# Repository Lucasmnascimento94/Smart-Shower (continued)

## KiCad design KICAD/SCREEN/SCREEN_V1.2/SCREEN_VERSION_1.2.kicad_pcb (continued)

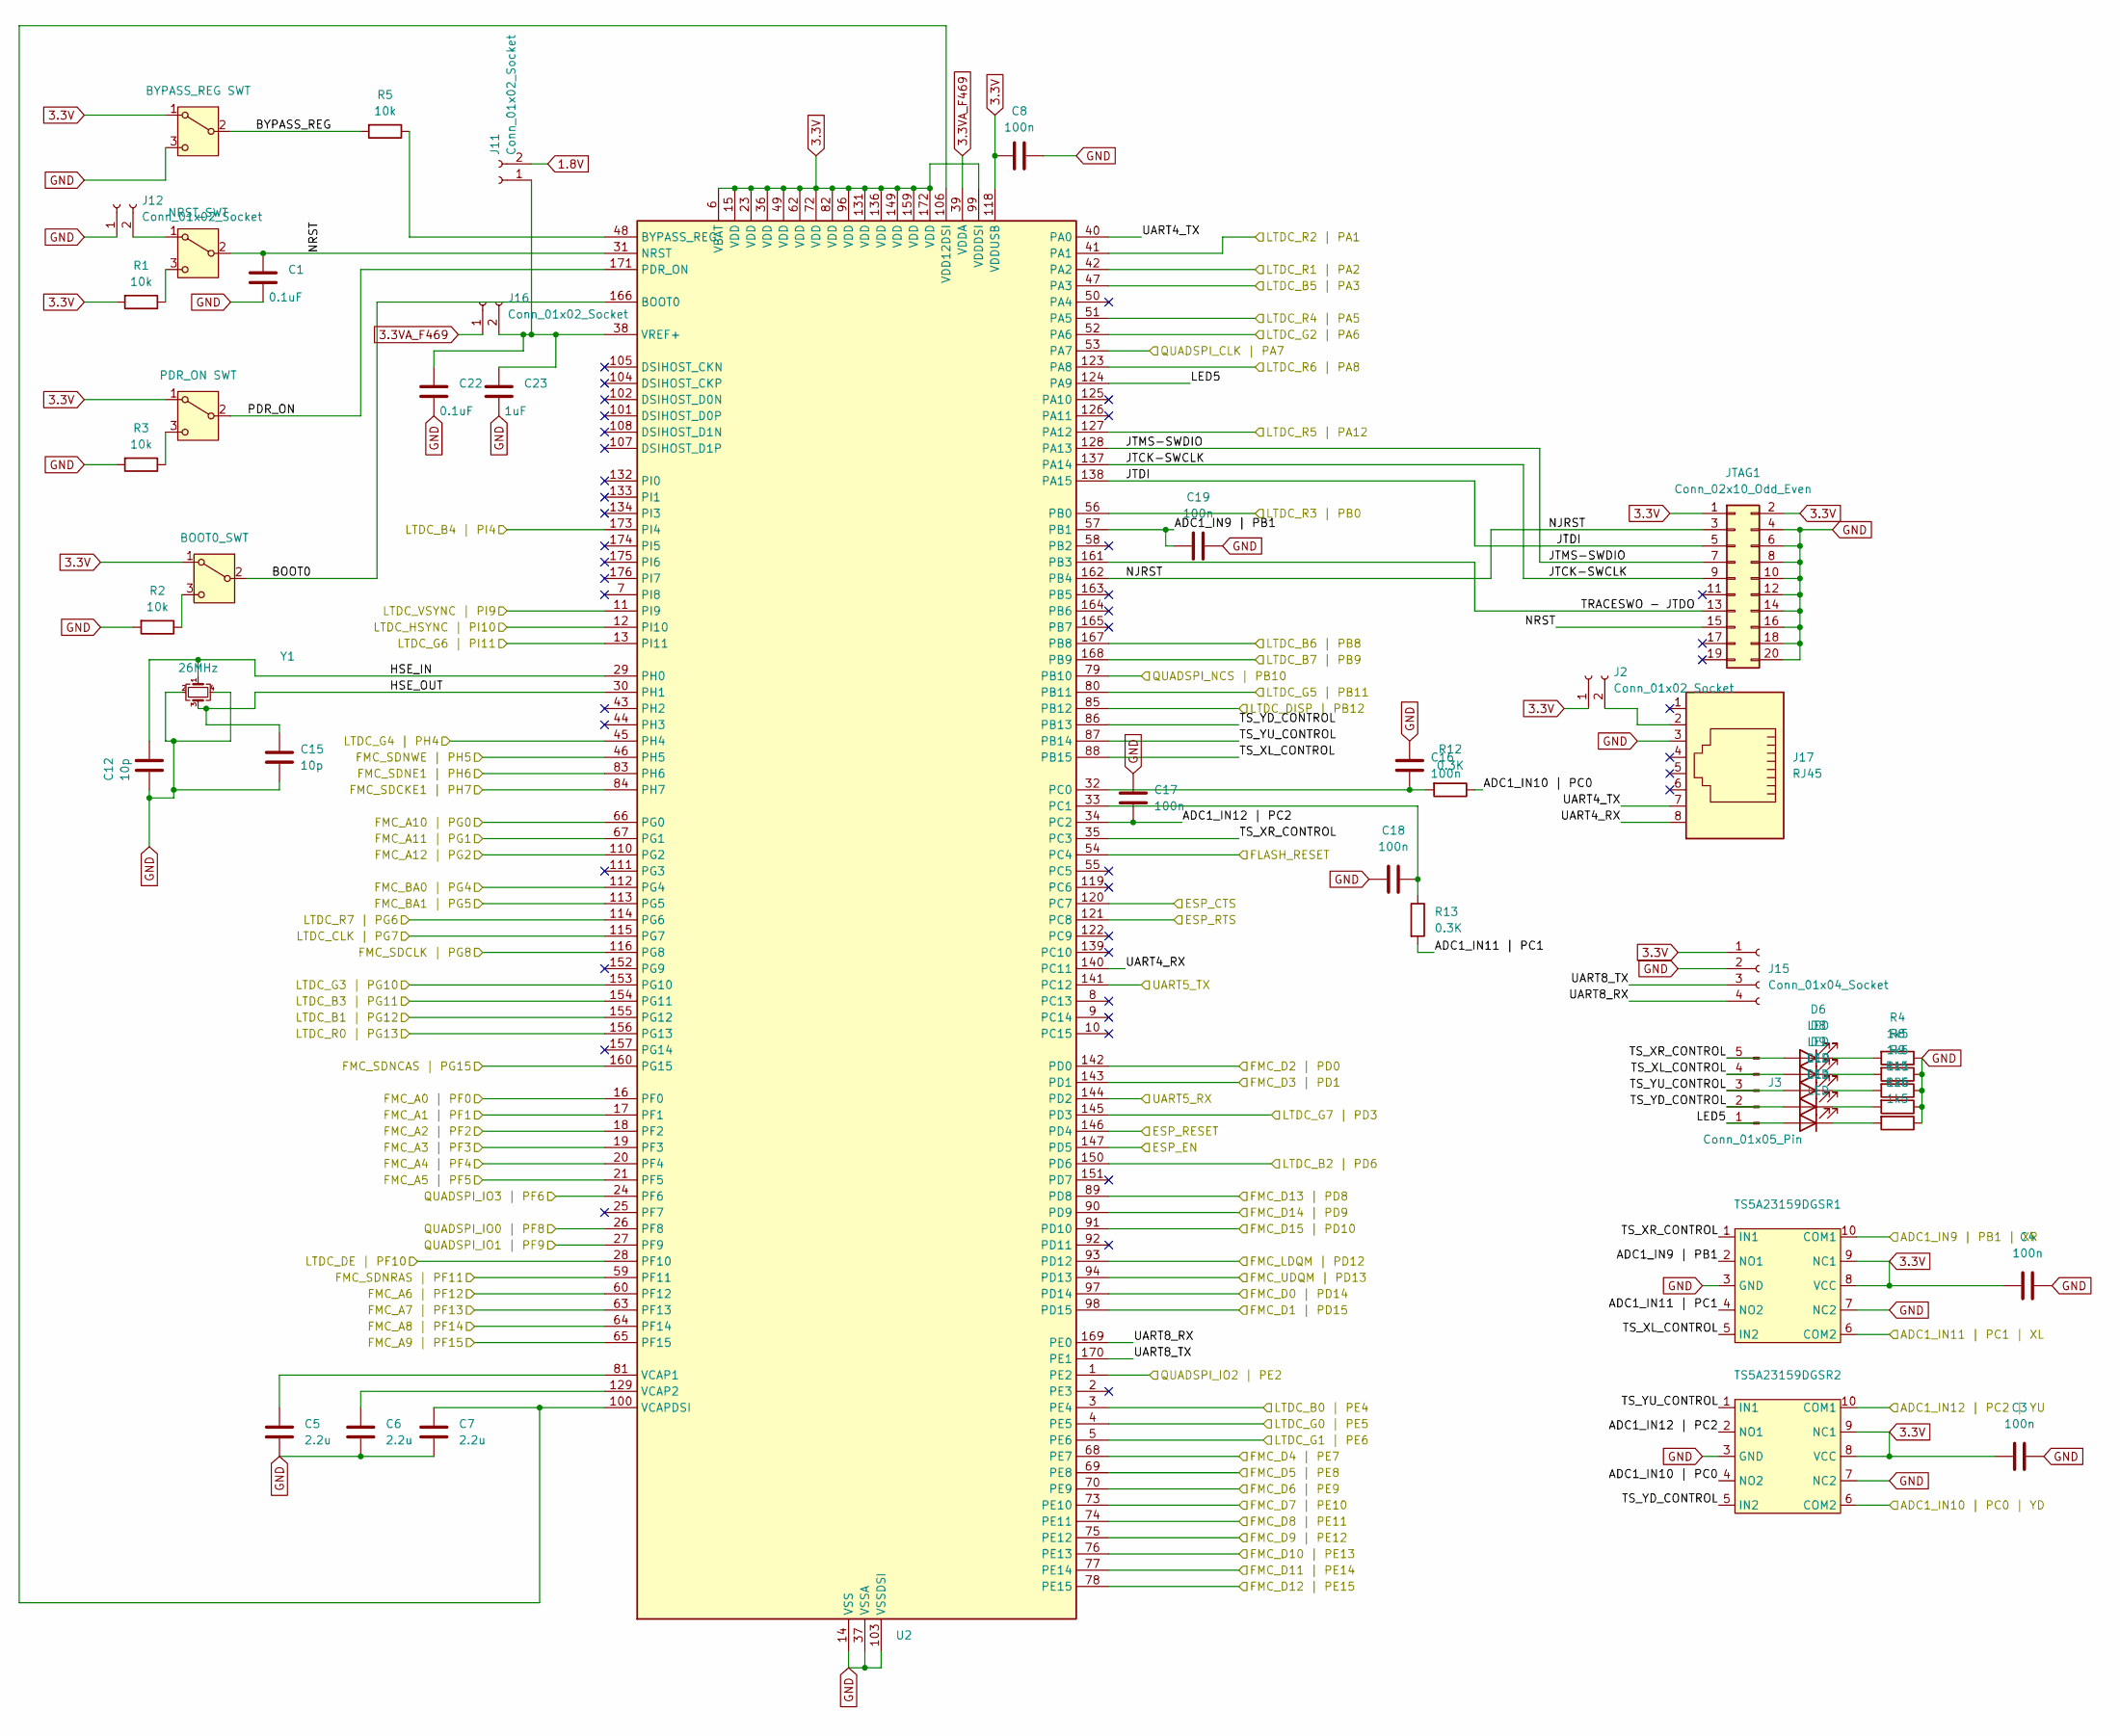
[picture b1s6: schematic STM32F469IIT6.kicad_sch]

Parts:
C1, C22: 0.1uF; C_0402_1005Metric
C3, C4, C8, C16, C17, C18, C19: 100n; C_0402_1005Metric
C5, C6, C7: 2.2u; C_0402_1005Metric
C12, C15: 10p; C_0402_1005Metric
C23: 1uF; C_0402_1005Metric
D6, D8, D9, D10, D11: LED; LED_0603_1608Metric
J2, J11, J12, J16: Conn_01x02_Socket; PinSocket_1x02_P2.54mm_Vertical
J3: Conn_01x05_Pin; PinSocket_1x05_P2.54mm_Vertical
J15: Conn_01x04_Socket; PinSocket_1x04_P2.54mm_Vertical
J17: RJ45; RJ45_Pulse_JXD6-0001NL_Horizontal
JTAG1: Conn_02x10_Odd_Even; IDC-Header_2x10_P2.54mm_Vertical
R1, R2, R3, R5: 10k; R_0402_1005Metric
R4, R8, R9, R11, R26: 1k5; R_0402_1005Metric
R12, R13: 0.3K; R_0402_1005Metric
SW1: BOOT0_SWT; SW_Slide_SPDT_Straight_CK_OS102011MS2Q
SW2: NRST_SWT; SW_Slide_SPDT_Straight_CK_OS102011MS2Q
SW3: PDR_ON SWT; SW_Slide_SPDT_Straight_CK_OS102011MS2Q
SW4: BYPASS_REG SWT; SW_Slide_SPDT_Straight_CK_OS102011MS2Q
TS5A23159DGSR1, TS5A23159DGSR2: TS5A23159DGSR
U2: STM32F469IITx; LQFP-176_24x24mm_P0.5mm
Y1: 26MHz; Crystal_SMD_3225-4Pin_3.2x2.5mm_HandSoldering

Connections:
1.8V: J11.2; also elsewhere on the board
3.3V: C3.1, C4.1, C8.1, J2.1, J15.1, JTAG1.1, JTAG1.2, R1.2, SW1.1 (A), SW3.1 (A), SW4.1 (A), TS5A23159DGSR1.8 (VCC), TS5A23159DGSR1.9 (NC1), TS5A23159DGSR2.8 (VCC), TS5A23159DGSR2.9 (NC1), U2.6 (VBAT), U2.15 (VDD), U2.23 (VDD), U2.36 (VDD), U2.49 (VDD), U2.62 (VDD), U2.72 (VDD), U2.82 (VDD), U2.96 (VDD), U2.99 (VDDDSI), U2.118 (VDDUSB), U2.131 (VDD), U2.136 (VDD), U2.149 (VDD), U2.159 (VDD), U2.172 (VDD); also elsewhere on the board
3.3VA_F469: J16.1, U2.39 (VDDA); also elsewhere on the board
/ESP-12E/CTS: U2.120 (PC7); also elsewhere on the board
/ESP-12E/EN: U2.147 (PD5); also elsewhere on the board
/ESP-12E/ESP_RX: U2.141 (PC12); also elsewhere on the board
/ESP-12E/ESP_TX: U2.144 (PD2); also elsewhere on the board
/ESP-12E/RST: U2.146 (PD4); also elsewhere on the board
/ESP-12E/RTS: U2.121 (PC8); also elsewhere on the board
/Flash - W25M512JVFIQ TR/CLK: U2.53 (PA7); also elsewhere on the board
/Flash - W25M512JVFIQ TR/CS: U2.79 (PB10); also elsewhere on the board
/Flash - W25M512JVFIQ TR/IO0: U2.26 (PF8); also elsewhere on the board
/Flash - W25M512JVFIQ TR/IO1: U2.27 (PF9); also elsewhere on the board
/Flash - W25M512JVFIQ TR/IO2: U2.1 (PE2); also elsewhere on the board
/Flash - W25M512JVFIQ TR/IO3: U2.24 (PF6); also elsewhere on the board
/Flash - W25M512JVFIQ TR/RESET: U2.54 (PC4); also elsewhere on the board
/LCD/B0: U2.3 (PE4); also elsewhere on the board
/LCD/B1: U2.155 (PG12); also elsewhere on the board
/LCD/B2: U2.150 (PD6); also elsewhere on the board
/LCD/B3: U2.154 (PG11); also elsewhere on the board
/LCD/B4: U2.173 (PI4); also elsewhere on the board
/LCD/B5: U2.47 (PA3); also elsewhere on the board
/LCD/B6: U2.167 (PB8); also elsewhere on the board
/LCD/B7: U2.168 (PB9); also elsewhere on the board
/LCD/DCLK: U2.115 (PG7); also elsewhere on the board
/LCD/DEN: U2.28 (PF10); also elsewhere on the board
/LCD/DISP: U2.85 (PB12); also elsewhere on the board
/LCD/G0: U2.4 (PE5); also elsewhere on the board
/LCD/G1: U2.5 (PE6); also elsewhere on the board
/LCD/G2: U2.52 (PA6); also elsewhere on the board
/LCD/G3: U2.153 (PG10); also elsewhere on the board
/LCD/G4: U2.45 (PH4); also elsewhere on the board
/LCD/G5: U2.80 (PB11); also elsewhere on the board
/LCD/G6: U2.13 (PI11); also elsewhere on the board
/LCD/G7: U2.145 (PD3); also elsewhere on the board
/LCD/HSYNC: U2.12 (PI10); also elsewhere on the board
/LCD/R0: U2.156 (PG13); also elsewhere on the board
/LCD/R1: U2.42 (PA2); also elsewhere on the board
/LCD/R2: U2.41 (PA1); also elsewhere on the board
/LCD/R3: U2.56 (PB0); also elsewhere on the board
/LCD/R4: U2.51 (PA5); also elsewhere on the board
/LCD/R5: U2.127 (PA12); also elsewhere on the board
/LCD/R6: U2.123 (PA8); also elsewhere on the board
/LCD/R7: U2.114 (PG6); also elsewhere on the board
/LCD/VSYNC: U2.11 (PI9); also elsewhere on the board
/LCD/XL_ADC: TS5A23159DGSR1.6 (COM2); also elsewhere on the board
/LCD/XR_ADC: TS5A23159DGSR1.10 (COM1); also elsewhere on the board
/LCD/YD_ADC: TS5A23159DGSR2.6 (COM2); also elsewhere on the board
/LCD/YU_ADC: TS5A23159DGSR2.10 (COM1); also elsewhere on the board
/STM32F469IIT6/ADC1_IN9 | PB1: C19.1, TS5A23159DGSR1.2 (NO1), U2.57 (PB1)
/STM32F469IIT6/ADC1_IN10 | PC0: R12.1, TS5A23159DGSR2.4 (NO2)
/STM32F469IIT6/ADC1_IN11 | PC1: R13.2, TS5A23159DGSR1.4 (NO2)
/STM32F469IIT6/ADC1_IN12 | PC2: C17.2, TS5A23159DGSR2.2 (NO1), U2.34 (PC2)
/STM32F469IIT6/BOOT0: SW1.2 (B), U2.166 (BOOT0); also elsewhere on the board
/STM32F469IIT6/BYPASS_REG: R5.2, SW4.2 (B); also elsewhere on the board
/STM32F469IIT6/FMC_A0 | PF0: U2.16 (PF0); also elsewhere on the board
/STM32F469IIT6/FMC_A1 | PF1: U2.17 (PF1); also elsewhere on the board
/STM32F469IIT6/FMC_A2 | PF2: U2.18 (PF2); also elsewhere on the board
/STM32F469IIT6/FMC_A3 | PF3: U2.19 (PF3); also elsewhere on the board
/STM32F469IIT6/FMC_A4 | PF4: U2.20 (PF4); also elsewhere on the board
/STM32F469IIT6/FMC_A5 | PF5: U2.21 (PF5); also elsewhere on the board
/STM32F469IIT6/FMC_A6 | PF12: U2.60 (PF12); also elsewhere on the board
/STM32F469IIT6/FMC_A7 | PF13: U2.63 (PF13); also elsewhere on the board
/STM32F469IIT6/FMC_A8 | PF14: U2.64 (PF14); also elsewhere on the board
/STM32F469IIT6/FMC_A9 | PF15: U2.65 (PF15); also elsewhere on the board
/STM32F469IIT6/FMC_A10 | PG0: U2.66 (PG0); also elsewhere on the board
/STM32F469IIT6/FMC_A11 | PG1: U2.67 (PG1); also elsewhere on the board
/STM32F469IIT6/FMC_A12 | PG2: U2.110 (PG2); also elsewhere on the board
/STM32F469IIT6/FMC_BA0 | PG4: U2.112 (PG4); also elsewhere on the board
/STM32F469IIT6/FMC_BA1 | PG5: U2.113 (PG5); also elsewhere on the board
/STM32F469IIT6/FMC_D0 | PD14: U2.97 (PD14); also elsewhere on the board
/STM32F469IIT6/FMC_D1 | PD15: U2.98 (PD15); also elsewhere on the board
/STM32F469IIT6/FMC_D2 | PD0: U2.142 (PD0); also elsewhere on the board
/STM32F469IIT6/FMC_D3 | PD1: U2.143 (PD1); also elsewhere on the board
/STM32F469IIT6/FMC_D4 | PE7: U2.68 (PE7); also elsewhere on the board
/STM32F469IIT6/FMC_D5 | PE8: U2.69 (PE8); also elsewhere on the board
/STM32F469IIT6/FMC_D6 | PE9: U2.70 (PE9); also elsewhere on the board
/STM32F469IIT6/FMC_D7 | PE10: U2.73 (PE10); also elsewhere on the board
/STM32F469IIT6/FMC_D8 | PE11: U2.74 (PE11); also elsewhere on the board
/STM32F469IIT6/FMC_D9 | PE12: U2.75 (PE12); also elsewhere on the board
/STM32F469IIT6/FMC_D10 | PE13: U2.76 (PE13); also elsewhere on the board
/STM32F469IIT6/FMC_D11 | PE14: U2.77 (PE14); also elsewhere on the board
/STM32F469IIT6/FMC_D12 | PE15: U2.78 (PE15); also elsewhere on the board
/STM32F469IIT6/FMC_D13 | PD8: U2.89 (PD8); also elsewhere on the board
/STM32F469IIT6/FMC_D14 | PD9: U2.90 (PD9); also elsewhere on the board
/STM32F469IIT6/FMC_D15 | PD10: U2.91 (PD10); also elsewhere on the board
/STM32F469IIT6/FMC_LDQM | PD12: U2.93 (PD12); also elsewhere on the board
/STM32F469IIT6/FMC_SDCKE1 | PH7: U2.84 (PH7); also elsewhere on the board
/STM32F469IIT6/FMC_SDCLK | PG8: U2.116 (PG8); also elsewhere on the board
/STM32F469IIT6/FMC_SDNCAS | PG15: U2.160 (PG15); also elsewhere on the board
/STM32F469IIT6/FMC_SDNE1 | PH6: U2.83 (PH6); also elsewhere on the board
/STM32F469IIT6/FMC_SDNRAS | PF11: U2.59 (PF11); also elsewhere on the board
/STM32F469IIT6/FMC_SDNWE | PH5: U2.46 (PH5); also elsewhere on the board
/STM32F469IIT6/FMC_UDQM | PD13: U2.94 (PD13); also elsewhere on the board
/STM32F469IIT6/HSE_IN: C12.1, U2.29 (PH0), Y1.1
/STM32F469IIT6/HSE_OUT: C15.1, U2.30 (PH1), Y1.3
/STM32F469IIT6/JTCK-SWCLK: JTAG1.9, U2.137 (PA14)
/STM32F469IIT6/JTDI: JTAG1.5, U2.138 (PA15)
/STM32F469IIT6/JTMS-SWDIO: JTAG1.7, U2.128 (PA13)
/STM32F469IIT6/LED5: D11.2 (A), J3.1, U2.124 (PA9)
/STM32F469IIT6/NJRST: JTAG1.3, U2.162 (PB4)
/STM32F469IIT6/NRST: C1.2, JTAG1.15, SW2.2 (B), U2.31 (NRST); also elsewhere on the board
/STM32F469IIT6/PDR_ON: SW3.2 (B), U2.171 (PDR_ON); also elsewhere on the board
/STM32F469IIT6/TRACESWO - JTDO: JTAG1.13, U2.161 (PB3)
/STM32F469IIT6/TS_XL_CONTROL: D8.2 (A), J3.4, TS5A23159DGSR1.5 (IN2), U2.88 (PB15)
/STM32F469IIT6/TS_XR_CONTROL: D6.2 (A), J3.5, TS5A23159DGSR1.1 (IN1), U2.35 (PC3)
/STM32F469IIT6/TS_YD_CONTROL: D10.2 (A), J3.2, TS5A23159DGSR2.5 (IN2), U2.86 (PB13)
/STM32F469IIT6/TS_YU_CONTROL: D9.2 (A), J3.3, TS5A23159DGSR2.1 (IN1), U2.87 (PB14)
/STM32F469IIT6/UART4_RX: J17.8, U2.140 (PC11)
/STM32F469IIT6/UART4_TX: J17.7, U2.40 (PA0)
/STM32F469IIT6/UART8_RX: J15.4, U2.169 (PE0)
/STM32F469IIT6/UART8_TX: J15.3, U2.170 (PE1)
GND: C1.1, C3.2, C4.2, C5.2, C6.2, C7.2, C8.2, C12.2, C15.2, C16.1, C17.1, C18.1, C19.2, C22.1, C23.1, J12.1, J15.2, J17.3, JTAG1.4, JTAG1.6, JTAG1.8, JTAG1.10, JTAG1.12, JTAG1.14, JTAG1.16, JTAG1.18, JTAG1.20, R2.2, R3.2, R4.1, R8.1, R9.1, R11.1, R26.1, SW4.3 (C), TS5A23159DGSR1.3 (GND), TS5A23159DGSR1.7 (NC2), TS5A23159DGSR2.3 (GND), TS5A23159DGSR2.7 (NC2), U2.14 (VSS), U2.22 (VSS), U2.37 (VSSA), U2.61 (VSS), U2.71 (VSS), U2.95 (VSS), U2.103 (VSSDSI), U2.109 (VSSDSI), U2.117 (VSS), U2.130 (VSS), U2.135 (VSS), U2.148 (VSS), U2.158 (VSS), Y1.2, Y1.4; also elsewhere on the board
unnamed: D6.1 (K), R4.2
unnamed: D8.1 (K), R8.2
unnamed: D9.1 (K), R9.2
unnamed: D10.1 (K), R11.2
unnamed: D11.1 (K), R26.2
unnamed: J2.2, J17.2
unnamed: C22.2, C23.2, J11.1, J16.2, U2.38 (VREF+)
unnamed 137: J12.2, SW2.1 (A); also elsewhere on the board
unnamed 140: R2.1, SW1.3 (C); also elsewhere on the board
unnamed 141: R1.1, SW2.3 (C); also elsewhere on the board
unnamed 142: R3.1, SW3.3 (C); also elsewhere on the board
unnamed: R5.1, U2.48 (BYPASS_REG)
unnamed: C16.2, R12.2, U2.32 (PC0)
unnamed: C18.2, R13.1, U2.33 (PC1)
unnamed: C5.1, U2.81 (VCAP1)
unnamed: C6.1, U2.129 (VCAP2)
unnamed: C7.1, U2.100 (VCAPDSI), U2.106 (VDD12DSI)

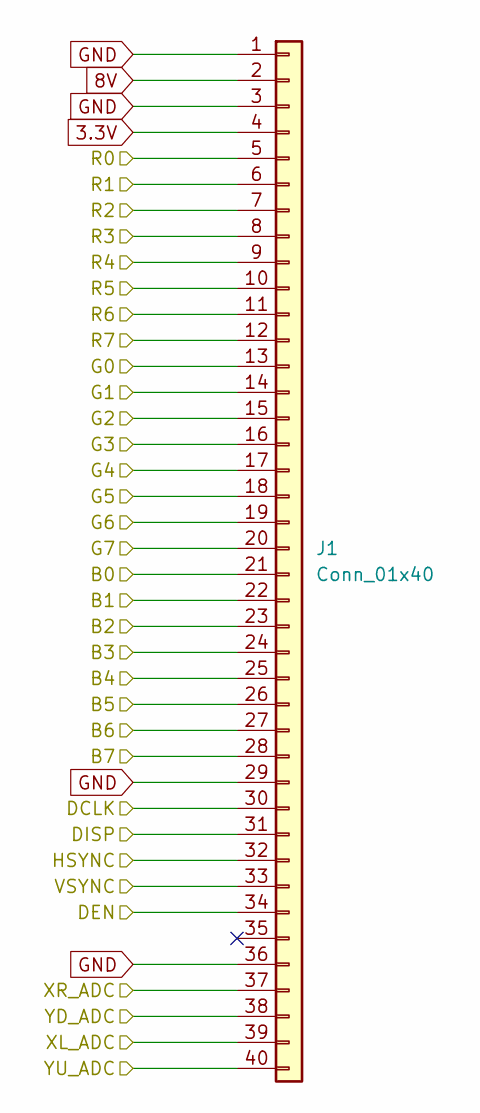
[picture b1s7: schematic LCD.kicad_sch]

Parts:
J1: Conn_01x40; Hirose_FH12-40S-0.5SH_1x40-1MP_P0.50mm_Horizontal

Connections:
3.3V: J1.4; also elsewhere on the board
8V: J1.2; also elsewhere on the board
/LCD/B0: J1.21; also elsewhere on the board
/LCD/B1: J1.22; also elsewhere on the board
/LCD/B2: J1.23; also elsewhere on the board
/LCD/B3: J1.24; also elsewhere on the board
/LCD/B4: J1.25; also elsewhere on the board
/LCD/B5: J1.26; also elsewhere on the board
/LCD/B6: J1.27; also elsewhere on the board
/LCD/B7: J1.28; also elsewhere on the board
/LCD/DCLK: J1.30; also elsewhere on the board
/LCD/DEN: J1.34; also elsewhere on the board
/LCD/DISP: J1.31; also elsewhere on the board
/LCD/G0: J1.13; also elsewhere on the board
/LCD/G1: J1.14; also elsewhere on the board
/LCD/G2: J1.15; also elsewhere on the board
/LCD/G3: J1.16; also elsewhere on the board
/LCD/G4: J1.17; also elsewhere on the board
/LCD/G5: J1.18; also elsewhere on the board
/LCD/G6: J1.19; also elsewhere on the board
/LCD/G7: J1.20; also elsewhere on the board
/LCD/HSYNC: J1.32; also elsewhere on the board
/LCD/R0: J1.5; also elsewhere on the board
/LCD/R1: J1.6; also elsewhere on the board
/LCD/R2: J1.7; also elsewhere on the board
/LCD/R3: J1.8; also elsewhere on the board
/LCD/R4: J1.9; also elsewhere on the board
/LCD/R5: J1.10; also elsewhere on the board
/LCD/R6: J1.11; also elsewhere on the board
/LCD/R7: J1.12; also elsewhere on the board
/LCD/VSYNC: J1.33; also elsewhere on the board
/LCD/XL_ADC: J1.39; also elsewhere on the board
/LCD/XR_ADC: J1.37; also elsewhere on the board
/LCD/YD_ADC: J1.38; also elsewhere on the board
/LCD/YU_ADC: J1.40; also elsewhere on the board
GND: J1.1, J1.3, J1.29, J1.36; also elsewhere on the board

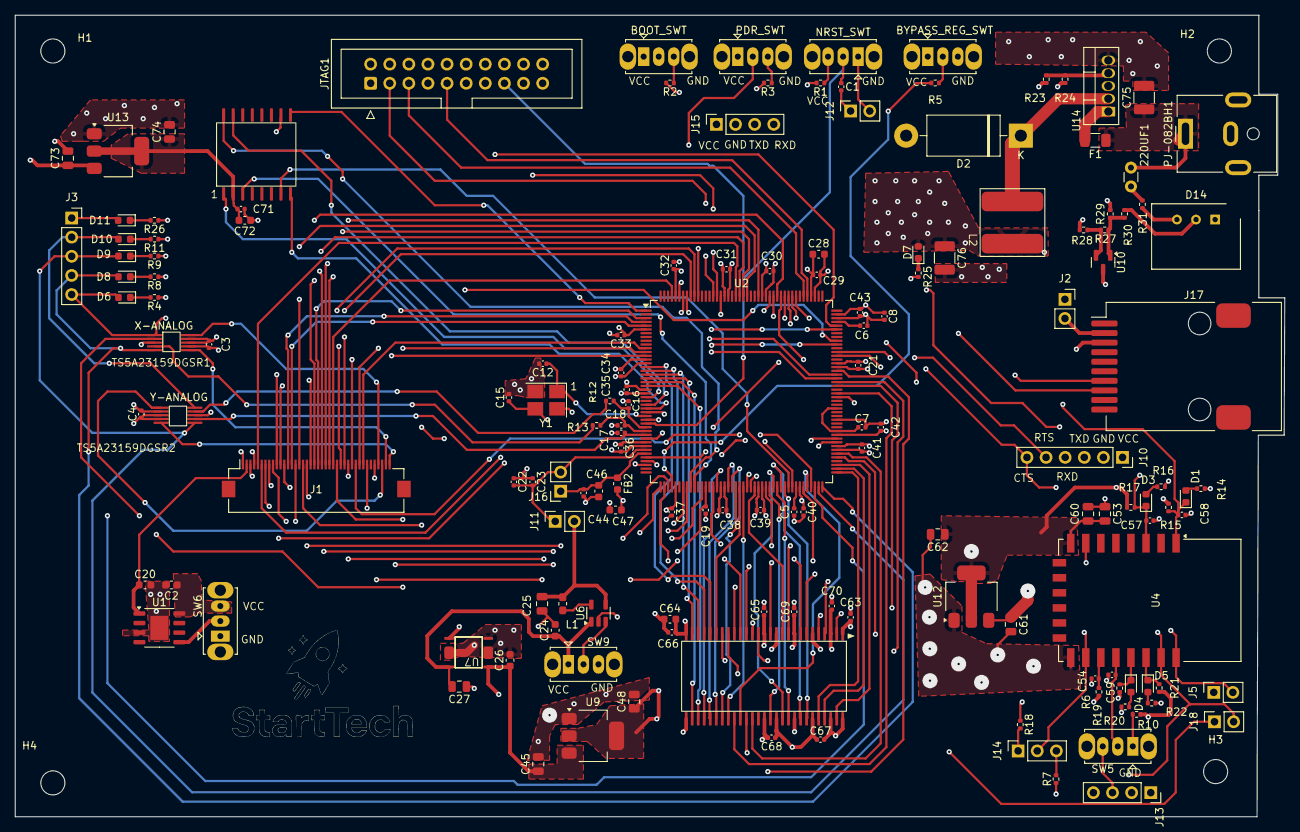
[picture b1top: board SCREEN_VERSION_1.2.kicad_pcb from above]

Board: 6 copper layers, 168.7 x 106.5 mm, 154 parts (0 on the bottom side), 161 nets.

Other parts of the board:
BOOT_SWT: BOOT0_SWT; SW_Slide_SPDT_Straight_CK_OS102011MS2Q
BYPASS_REG_SWT: BYPASS_REG SWT; SW_Slide_SPDT_Straight_CK_OS102011MS2Q
NRST_SWT: NRST_SWT; SW_Slide_SPDT_Straight_CK_OS102011MS2Q
PDR_SWT: PDR_ON SWT; SW_Slide_SPDT_Straight_CK_OS102011MS2Q

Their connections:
3.3V: BOOT_SWT.1 (A), BYPASS_REG_SWT.1 (A), PDR_SWT.1 (A); also elsewhere on the board
/STM32F469IIT6/BOOT0: BOOT_SWT.2 (B); also elsewhere on the board
/STM32F469IIT6/BYPASS_REG: BYPASS_REG_SWT.2 (B); also elsewhere on the board
/STM32F469IIT6/NRST: NRST_SWT.2 (B); also elsewhere on the board
/STM32F469IIT6/PDR_ON: PDR_SWT.2 (B); also elsewhere on the board
GND: BYPASS_REG_SWT.3 (C); also elsewhere on the board
unnamed 137: NRST_SWT.1 (A); also elsewhere on the board
unnamed 140: BOOT_SWT.3 (C); also elsewhere on the board
unnamed 141: NRST_SWT.3 (C); also elsewhere on the board
unnamed 142: PDR_SWT.3 (C); also elsewhere on the board

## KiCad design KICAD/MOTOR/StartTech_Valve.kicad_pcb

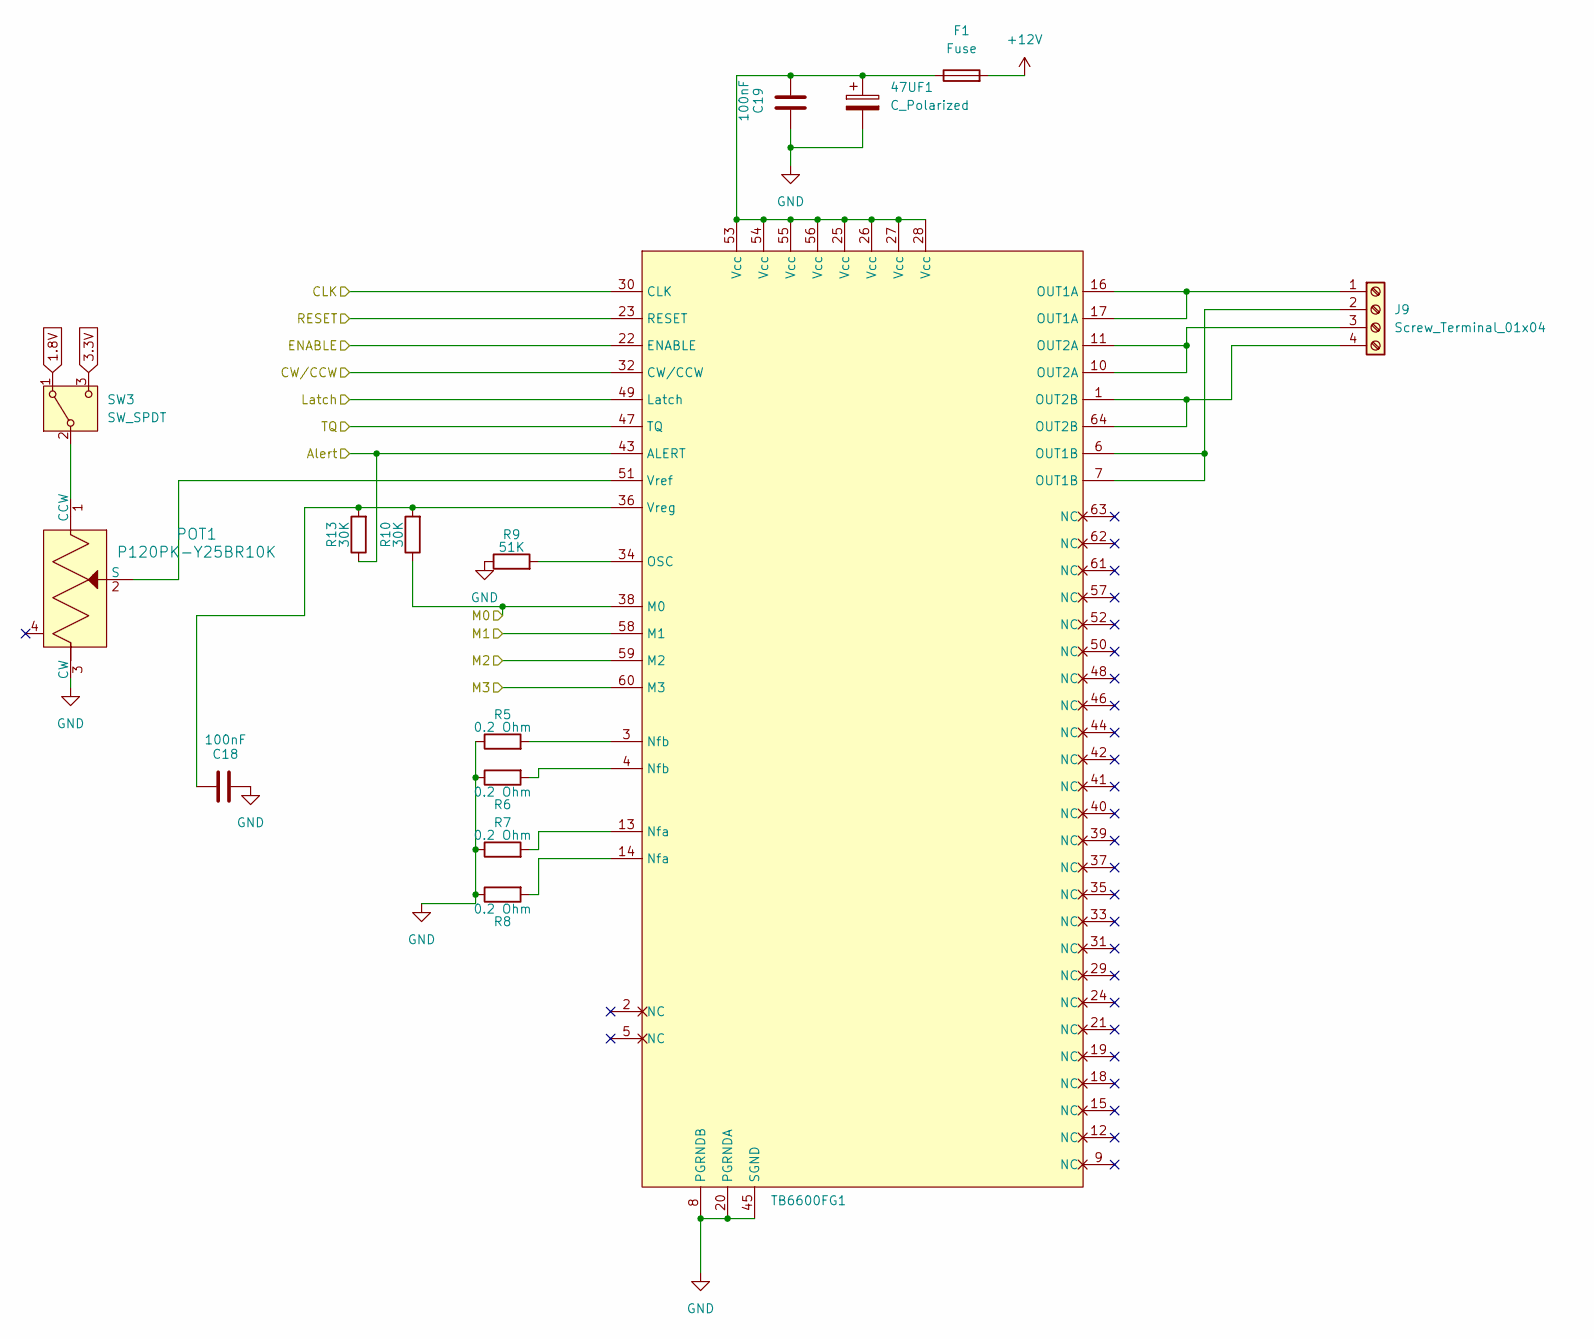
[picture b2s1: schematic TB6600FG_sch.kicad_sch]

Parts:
47UF1: C_Polarized; C_Disc_D3.0mm_W1.6mm_P2.50mm
C18, C19: 100nF; C_0402_1005Metric
F1: Fuse; Fuse_0402_1005Metric_Pad0.77x0.64mm_HandSolder
J9: Screw_Terminal_01x04; SCREWCON - 4PIN
POT1: P120PK-Y25BR10K; Potentiometer_P120PK-Y25BR10K; MPN P120PK-Y25BR10K; Digi-Key_PN 987-1710-ND
R5, R6, R7, R8: 0.2 Ohm; R_0402_1005Metric
R9: 51K; R_0402_1005Metric
R10, R13: 30K; R_0402_1005Metric
SW3: SW_SPDT; SW_Slide_SPDT_Straight_CK_OS102011MS2Q
TB6600FG1: TB6600FG

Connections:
1.8V: SW3.1 (A); also elsewhere on the board
3.3V: SW3.3 (C); also elsewhere on the board
+12V: F1.2; also elsewhere on the board
/STM32F411RCT6/Valve_ALERT: R13.1, TB6600FG1.43 (ALERT); also elsewhere on the board
/STM32F411RCT6/Valve_CCW: TB6600FG1.32 (CW/CCW); also elsewhere on the board
/STM32F411RCT6/Valve_CLK: TB6600FG1.30 (CLK); also elsewhere on the board
/STM32F411RCT6/Valve_EN: TB6600FG1.22 (ENABLE); also elsewhere on the board
/STM32F411RCT6/Valve_LATCH: TB6600FG1.49 (Latch); also elsewhere on the board
/STM32F411RCT6/Valve_M0: R10.1, TB6600FG1.38 (M0); also elsewhere on the board
/STM32F411RCT6/Valve_M1: TB6600FG1.58 (M1); also elsewhere on the board
/STM32F411RCT6/Valve_M2: TB6600FG1.59 (M2); also elsewhere on the board
/STM32F411RCT6/Valve_M3: TB6600FG1.60 (M3); also elsewhere on the board
/STM32F411RCT6/Valve_RST: TB6600FG1.23 (RESET); also elsewhere on the board
/STM32F411RCT6/Valve_TQ: TB6600FG1.47 (TQ); also elsewhere on the board
GND: 47UF1.2, C18.2, C19.1, POT1.3 (CW), R5.1, R6.1, R7.1, R8.1, R9.1, TB6600FG1.8 (PGRNDB), TB6600FG1.20 (PGRNDA), TB6600FG1.45 (SGND); also elsewhere on the board
unnamed: 47UF1.1, C19.2, F1.1, TB6600FG1.25 (Vcc), TB6600FG1.26 (Vcc), TB6600FG1.27 (Vcc), TB6600FG1.28 (Vcc), TB6600FG1.53 (Vcc), TB6600FG1.54 (Vcc), TB6600FG1.55 (Vcc), TB6600FG1.56 (Vcc)
unnamed: J9.1, TB6600FG1.16 (OUT1A), TB6600FG1.17 (OUT1A)
unnamed: J9.2, TB6600FG1.6 (OUT1B), TB6600FG1.7 (OUT1B)
unnamed: J9.3, TB6600FG1.10 (OUT2A), TB6600FG1.11 (OUT2A)
unnamed: J9.4, TB6600FG1.1 (OUT2B), TB6600FG1.64 (OUT2B)
unnamed: POT1.1 (CCW), SW3.2 (B)
unnamed: POT1.2 (S), TB6600FG1.51 (Vref)
unnamed: R5.2, TB6600FG1.3 (Nfb)
unnamed: R6.2, TB6600FG1.4 (Nfb)
unnamed: R7.2, TB6600FG1.13 (Nfa)
unnamed: R8.2, TB6600FG1.14 (Nfa)
unnamed: R9.2, TB6600FG1.34 (OSC)
unnamed: C18.1, R10.2, R13.2, TB6600FG1.36 (Vreg)

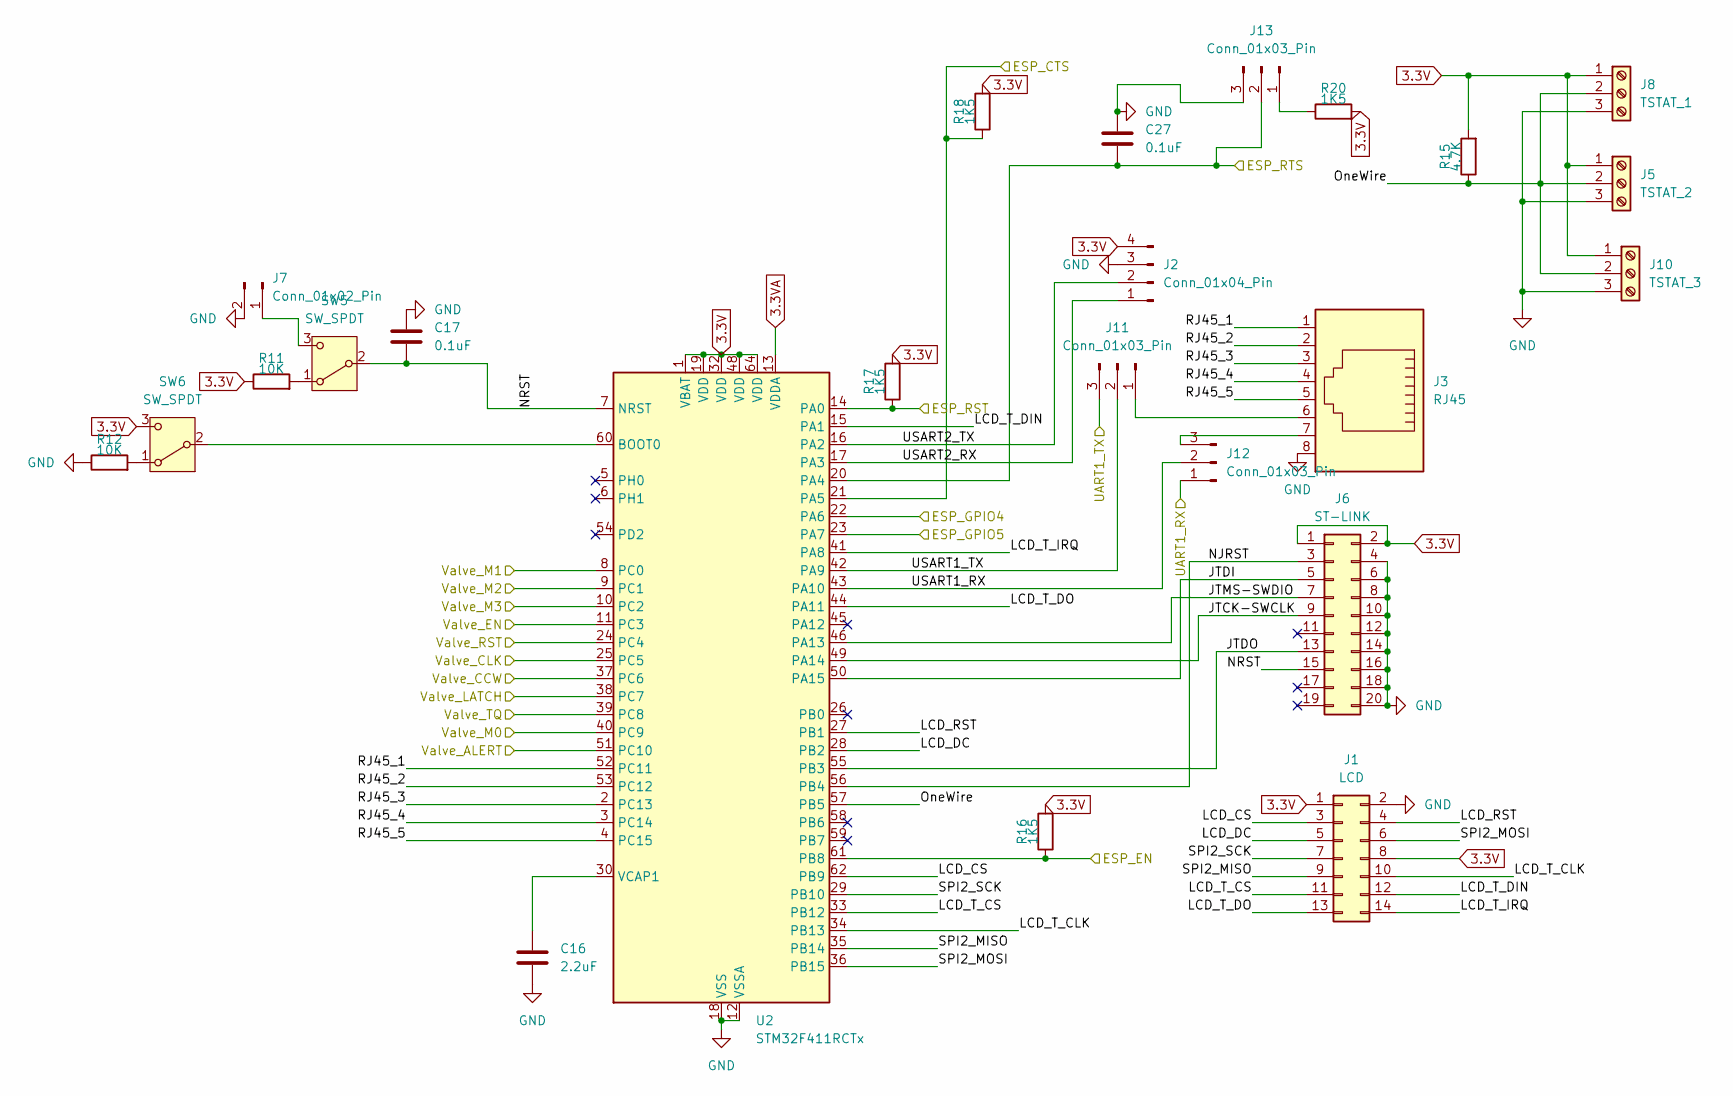
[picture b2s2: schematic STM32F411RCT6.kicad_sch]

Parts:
C16: 2.2uF; C_0603_1608Metric
C17, C27: 0.1uF; C_0402_1005Metric
J1: LCD; IDC-Header_2x07_P2.54mm_Vertical
J2: Conn_01x04_Pin; PinSocket_1x04_P2.54mm_Vertical
J3: RJ45; RJ45_Cetus_J1B1211CCD_Horizontal
J5: TSTAT_2; SCREWCON-3PIN
J6: ST-LINK; IDC-Header_2x10_P2.54mm_Vertical
J7: Conn_01x02_Pin; PinSocket_1x02_P2.54mm_Vertical
J8: TSTAT_1; SCREWCON-3PIN
J10: TSTAT_3; SCREWCON-3PIN
J11, J12, J13: Conn_01x03_Pin; PinSocket_1x03_P2.54mm_Vertical
R11, R12: 10K; R_0402_1005Metric
R15: 4.7K; R_0402_1005Metric
R16, R17, R18, R20: 1K5; R_0402_1005Metric
SW5, SW6: SW_SPDT; SW_Slide_SPDT_Straight_CK_OS102011MS2Q
U2: STM32F411RCTx; LQFP-64_10x10mm_P0.5mm

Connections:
3.3V: J1.1, J1.8, J2.4, J5.1, J6.1, J6.2, J8.1, J10.1, R11.1, R15.2, R16.2, R17.2, R18.2, R20.2, SW6.3 (C), U2.1 (VBAT), U2.19 (VDD), U2.32 (VDD), U2.48 (VDD), U2.64 (VDD); also elsewhere on the board
3.3VA: U2.13 (VDDA); also elsewhere on the board
/ESP-12E/CTS: R18.1, U2.21 (PA5); also elsewhere on the board
/ESP-12E/EN: R16.1, U2.61 (PB8); also elsewhere on the board
/ESP-12E/IO4: U2.22 (PA6); also elsewhere on the board
/ESP-12E/IO5: U2.23 (PA7); also elsewhere on the board
/ESP-12E/RST: R17.1, U2.14 (PA0); also elsewhere on the board
/ESP-12E/RTS: C27.2, J13.2, U2.20 (PA4); also elsewhere on the board
/ESP-12E/RXD: J11.3; also elsewhere on the board
/ESP-12E/TXD: J12.1; also elsewhere on the board
/STM32F411RCT6/JTCK-SWCLK: J6.9, U2.49 (PA14)
/STM32F411RCT6/JTDI: J6.5, U2.50 (PA15)
/STM32F411RCT6/JTDO: J6.13, U2.55 (PB3)
/STM32F411RCT6/JTMS-SWDIO: J6.7, U2.46 (PA13)
/STM32F411RCT6/LCD_CS: J1.3, U2.62 (PB9)
/STM32F411RCT6/LCD_DC: J1.5, U2.28 (PB2)
/STM32F411RCT6/LCD_RST: J1.4, U2.27 (PB1)
/STM32F411RCT6/LCD_T_CLK: J1.10, U2.34 (PB13)
/STM32F411RCT6/LCD_T_CS: J1.11, U2.33 (PB12)
/STM32F411RCT6/LCD_T_DIN: J1.12, U2.15 (PA1)
/STM32F411RCT6/LCD_T_DO: J1.13, U2.44 (PA11)
/STM32F411RCT6/LCD_T_IRQ: J1.14, U2.41 (PA8)
/STM32F411RCT6/NJRST: J6.3, U2.56 (PB4)
/STM32F411RCT6/NRST: C17.2, J6.15, SW5.2 (B), U2.7 (NRST)
/STM32F411RCT6/OneWire: J5.2, J8.2, J10.2, R15.1, U2.57 (PB5)
/STM32F411RCT6/RJ45_1: J3.1, U2.52 (PC11)
/STM32F411RCT6/RJ45_2: J3.2, U2.53 (PC12)
/STM32F411RCT6/RJ45_3: J3.3, U2.2 (PC13)
/STM32F411RCT6/RJ45_4: J3.4, U2.3 (PC14)
/STM32F411RCT6/RJ45_5: J3.5, U2.4 (PC15)
/STM32F411RCT6/SPI2_MISO: J1.9, U2.35 (PB14)
/STM32F411RCT6/SPI2_MOSI: J1.6, U2.36 (PB15)
/STM32F411RCT6/SPI2_SCK: J1.7, U2.29 (PB10)
/STM32F411RCT6/USART1_RX: J12.2, U2.43 (PA10)
/STM32F411RCT6/USART1_TX: J11.2, U2.42 (PA9)
/STM32F411RCT6/USART2_RX: J2.1, U2.17 (PA3)
/STM32F411RCT6/USART2_TX: J2.2, U2.16 (PA2)
/STM32F411RCT6/Valve_ALERT: U2.51 (PC10); also elsewhere on the board
/STM32F411RCT6/Valve_CCW: U2.37 (PC6); also elsewhere on the board
/STM32F411RCT6/Valve_CLK: U2.25 (PC5); also elsewhere on the board
/STM32F411RCT6/Valve_EN: U2.11 (PC3); also elsewhere on the board
/STM32F411RCT6/Valve_LATCH: U2.38 (PC7); also elsewhere on the board
/STM32F411RCT6/Valve_M0: U2.40 (PC9); also elsewhere on the board
/STM32F411RCT6/Valve_M1: U2.8 (PC0); also elsewhere on the board
/STM32F411RCT6/Valve_M2: U2.9 (PC1); also elsewhere on the board
/STM32F411RCT6/Valve_M3: U2.10 (PC2); also elsewhere on the board
/STM32F411RCT6/Valve_RST: U2.24 (PC4); also elsewhere on the board
/STM32F411RCT6/Valve_TQ: U2.39 (PC8); also elsewhere on the board
GND: C16.2, C17.1, C27.1, J1.2, J2.3, J3.8, J5.3, J6.4, J6.6, J6.8, J6.10, J6.12, J6.14, J6.16, J6.18, J6.20, J7.2, J8.3, J10.3, J13.3, R12.1, U2.12 (VSSA), U2.18 (VSS), U2.31 (VSS), U2.47 (VSS), U2.63 (VSS); also elsewhere on the board
unnamed: J7.1, SW5.3 (C)
unnamed: J3.6, J11.1
unnamed: J3.7, J12.3
unnamed: J13.1, R20.1
unnamed: R11.2, SW5.1 (A)
unnamed: R12.2, SW6.1 (A)
unnamed: SW6.2 (B), U2.60 (BOOT0)
unnamed: C16.1, U2.30 (VCAP1)
